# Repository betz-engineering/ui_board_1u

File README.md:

# ui_board_1u
A versatile user interface PCB, specifically designed for integration into the front-panel of a 1U height chassis.

__Featuring__

  * Rotary encoder
  * 2x RGB LEDs, brought to the front with light-pipes for mounting flexibility
  * 1x Tactile push button
  * 2.8" diagonal, 256 x 64 pixel OLED display with 16 shades (SSD1322)
  * All connected to a single 12 pin PMOD port

[__Schematic__](pics/ui_board_1u.pdf)

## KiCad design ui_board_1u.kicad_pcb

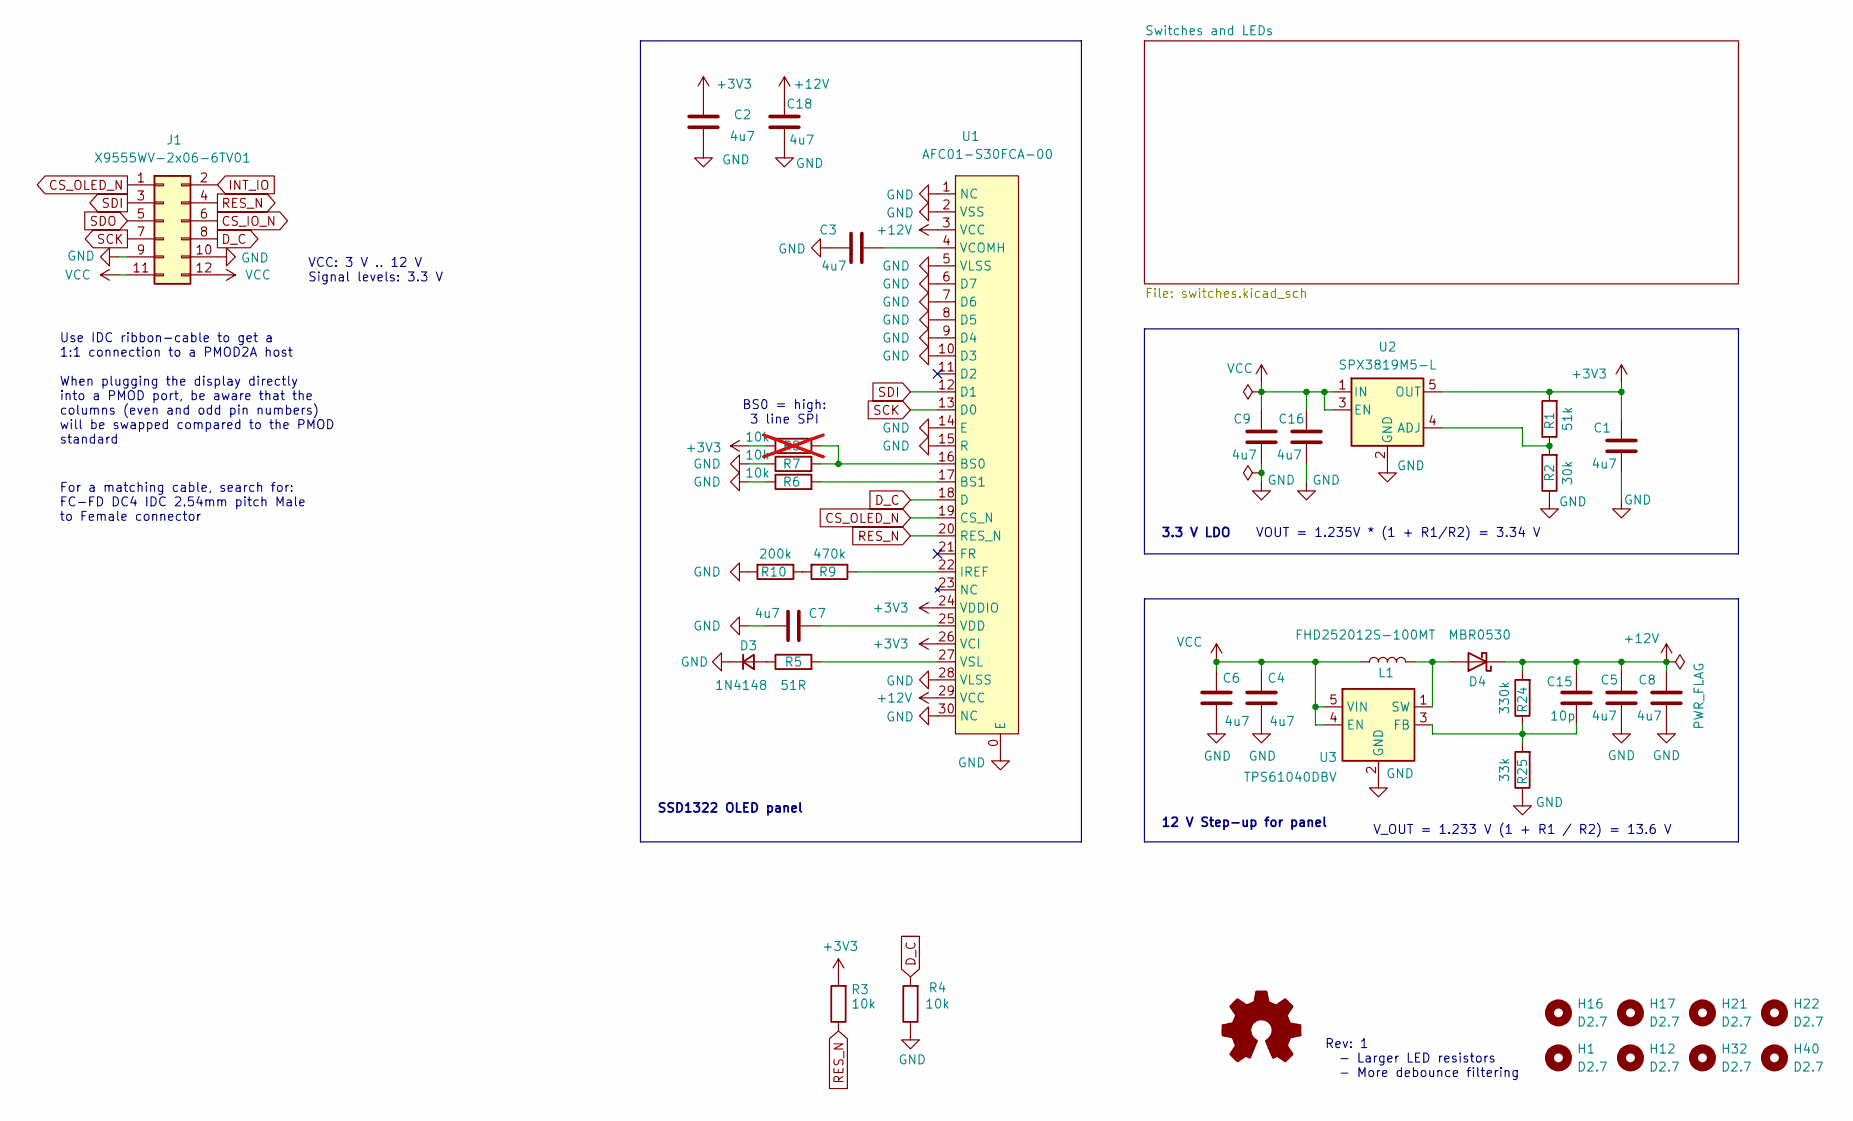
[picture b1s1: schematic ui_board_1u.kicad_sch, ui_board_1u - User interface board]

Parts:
C1, C2, C3, C4, C5, C6, C7, C8, C9, C16, C18: 4u7; C_1206_3216Metric
C15: 10p; C_0603_1608Metric
D3: 1N4148; D_SOD-323F
D4: MBR0530; D_SOD-123
H1, H12, H32, H40: D2.7; MountingHole_2.7mm_M2.5_ISO7380
H16, H17, H21, H22: D2.7; MountingHole_2.7mm_M2.5_ISO7380_Pad
J1: X9555WV-2x06-6TV01; IDC-Header_2x06_P2.54mm_Vertical
L1: FHD252012S-100MT; L_1008_2520Metric
R1: 51k; R_0603_1608Metric
R2: 30k; R_0603_1608Metric
R3, R4, R6, R7: 10k; R_0603_1608Metric
R5: 51R; R_0603_1608Metric
R8: 10k; R_0603_1608Metric; not fitted
R9: 470k; R_0603_1608Metric
R10: 200k; R_0603_1608Metric
R24: 330k; R_0603_1608Metric
R25: 33k; R_0603_1608Metric
U1: AFC01-S30FCA-00; oled_frame_2.8
U2: SPX3819M5-L; SOT-23-5; LCSC Part # C9056
U3: TPS61040DBV; SOT-23-5

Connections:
+3V3: C1.1, C2.1, R1.2, R3.2, R8.1, U1.24 (VDDIO), U1.26 (VCI), U2.5 (OUT); also elsewhere on the board
+12V: C5.1, C8.1, C15.1, C18.1, D4.1 (K), R24.2, U1.3 (VCC), U1.29 (VCC)
CS_IO_N: J1.6; also elsewhere on the board
CS_OLED_N: J1.1, U1.19 (CS_N)
D_C: J1.8, R4.2, U1.18 (D)
GND: C1.2, C2.2, C3.2, C4.2, C5.2, C6.2, C7.2, C8.2, C9.2, C16.2, C18.2, D3.1 (K), J1.9, J1.10, R2.1, R4.1, R6.1, R7.1, R10.2, R25.1, U1.0 (E), U1.1 (NC), U1.2 (VSS), U1.5 (VLSS), U1.6 (D7), U1.7 (D6), U1.8 (D5), U1.9 (D4), U1.10 (D3), U1.14 (E), U1.15 (R), U1.28 (VLSS), U1.30 (NC), U2.2 (GND), U3.2 (GND); also elsewhere on the board
INT_IO: J1.2; also elsewhere on the board
unnamed: D3.2 (A), R5.1
unnamed: D4.2 (A), L1.2, U3.1 (SW)
unnamed: R9.2, R10.1
unnamed: R7.2, R8.2, U1.16 (BS0)
unnamed: R6.2, U1.17 (BS1)
unnamed: R9.1, U1.22 (IREF)
unnamed: C3.1, U1.4 (VCOMH)
unnamed: C7.1, U1.25 (VDD)
unnamed: R5.2, U1.27 (VSL)
unnamed: R1.1, R2.2, U2.4 (ADJ)
unnamed: C15.2, R24.1, R25.2, U3.3 (FB)
RES_N: J1.4, R3.1, U1.20 (RES_N); also elsewhere on the board
SCK: J1.7, U1.13 (D0); also elsewhere on the board
SDI: J1.3, U1.12 (D1); also elsewhere on the board
SDO: J1.5; also elsewhere on the board
VCC: C4.1, C6.1, C9.1, C16.1, J1.11, J1.12, L1.1, U2.1 (IN), U2.3 (EN), U3.4 (EN), U3.5 (VIN)

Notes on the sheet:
12 V Step-up for panel
V_OUT = 1.233 V (1 + R1 / R2) = 13.6 V
Rev: 1 - Larger LED resistors - More debounce filtering
3.3 V LDO
Use IDC ribbon-cable to get a 1:1 connection to a PMOD2A host When plugging the display directly into a PMOD port, be aware that the columns (even and odd pin numbers) will be swapped compared to the PMOD standard
SSD1322 OLED panel
For a matching cable, search for: FC-FD DC4 IDC 2.54mm pitch Male to Female connector
BS0 = high: 3 line SPI
VOUT = 1.235V * (1 + R1/R2) = 3.34 V
VCC: 3 V .. 12 V Signal levels: 3.3 V

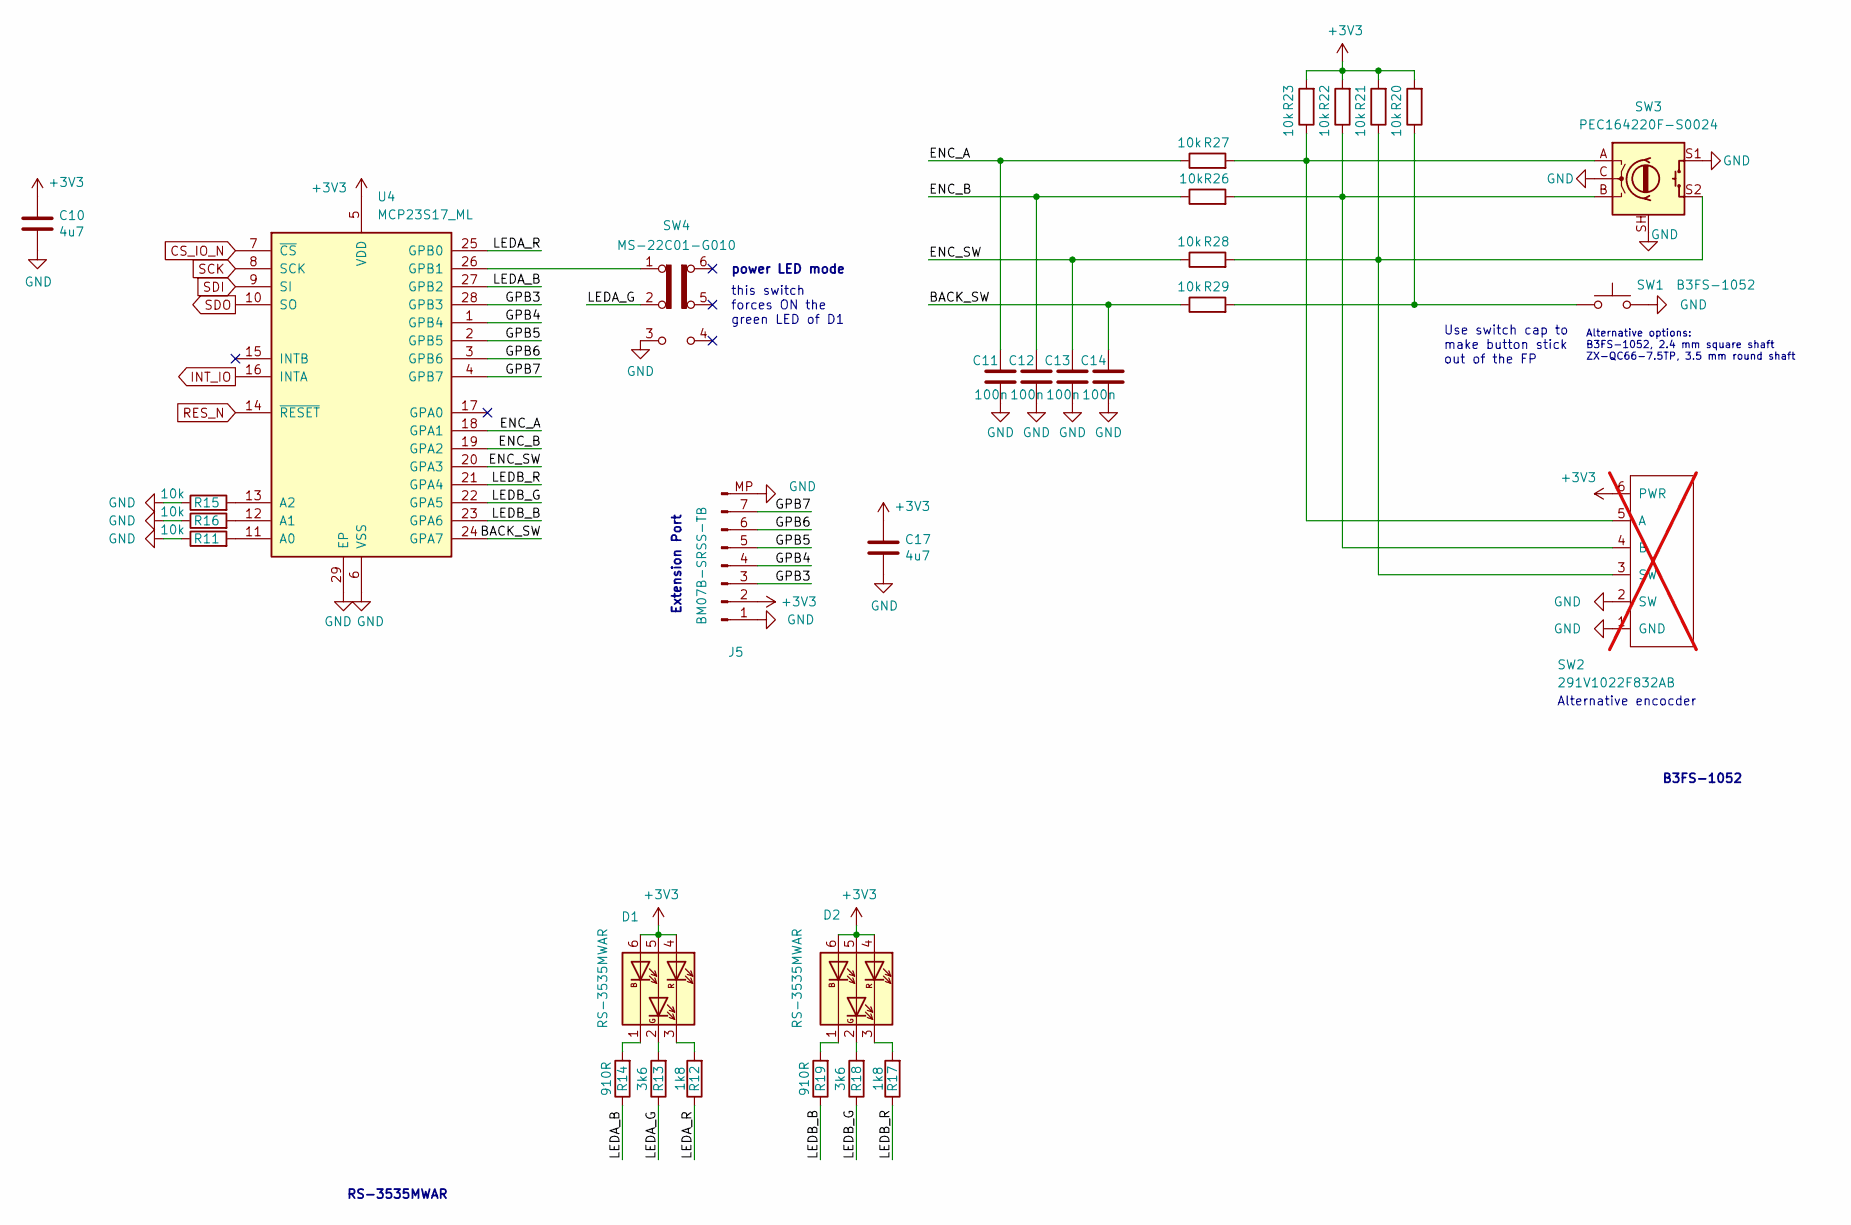
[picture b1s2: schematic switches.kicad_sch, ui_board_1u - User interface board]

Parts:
C10, C17: 4u7; C_1206_3216Metric
C11, C12, C13, C14: 100n; C_0603_1608Metric
D1, D2: RS-3535MWAR; LED_RGB_PLCC-6
J5: BM07B-SRSS-TB; JST_SH_BM07B-SRSS-TB_1x07-1MP_P1.00mm_Vertical; LCSC Part # C160393
R11, R15, R16, R20, R21, R22, R23, R26, R27, R28, R29: 10k; R_0603_1608Metric
R12, R17: 1k8; R_0603_1608Metric
R13, R18: 3k6; R_0603_1608Metric
R14, R19: 910R; R_0603_1608Metric
SW1: B3FS-1052; SW_SPST_Omron_B3FS-105xP
SW2: 291V1022F832AB; 291V1; digikey CT3044-ND; not fitted
SW3: PEC164220F-S0024; RotaryEncoder_Bourns_Vertical_PEC16-4xxxF-Sxxxx
SW4: MS-22C01-G010; MS-22C01
U4: MCP23S17_ML; QFN-28-1EP_6x6mm_P0.65mm_EP4.25x4.25mm

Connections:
+3V3: C10.1, C17.1, D1.4 (AR), D1.5 (AG), D1.6 (AB), D2.4 (AR), D2.5 (AG), D2.6 (AB), J5.2, R20.2, R21.2, R22.2, R23.2, SW2.6 (PWR), U4.5 (VDD); also elsewhere on the board
/Switches and LEDs/BACK_SW: C14.1, R29.1, U4.24 (GPA7)
/Switches and LEDs/ENC_A: C11.1, R27.1, U4.18 (GPA1)
/Switches and LEDs/ENC_B: C12.1, R26.1, U4.19 (GPA2)
/Switches and LEDs/ENC_SW: C13.1, R28.1, U4.20 (GPA3)
/Switches and LEDs/GPB3: J5.3, U4.28 (GPB3)
/Switches and LEDs/GPB4: J5.4, U4.1 (GPB4)
/Switches and LEDs/GPB5: J5.5, U4.2 (GPB5)
/Switches and LEDs/GPB6: J5.6, U4.3 (GPB6)
/Switches and LEDs/GPB7: J5.7, U4.4 (GPB7)
/Switches and LEDs/LEDA_B: R14.1, U4.27 (GPB2)
/Switches and LEDs/LEDA_G: R13.1, SW4.2 (B)
/Switches and LEDs/LEDA_R: R12.1, U4.25 (GPB0)
/Switches and LEDs/LEDB_B: R19.1, U4.23 (GPA6)
/Switches and LEDs/LEDB_G: R18.1, U4.22 (GPA5)
/Switches and LEDs/LEDB_R: R17.1, U4.21 (GPA4)
CS_IO_N: U4.7 (~CS); also elsewhere on the board
GND: C10.2, C11.2, C12.2, C13.2, C14.2, C17.2, J5.1, J5.MP, R11.1, R15.1, R16.1, SW1.2, SW2.1 (GND), SW2.2 (SW), SW3.C, SW3.S1, SW3.SH, SW4.3 (C), U4.6 (VSS), U4.29 (EP); also elsewhere on the board
INT_IO: U4.16 (INTA); also elsewhere on the board
unnamed: D1.1 (KB), R14.2
unnamed: D1.2 (KG), R13.2
unnamed: D1.3 (KR), R12.2
unnamed: D2.1 (KB), R19.2
unnamed: D2.2 (KG), R18.2
unnamed: D2.3 (KR), R17.2
unnamed: R20.1, R29.2, SW1.1
unnamed: R21.1, R28.2, SW2.3 (SW), SW3.S2
unnamed: R23.1, R27.2, SW2.5 (A), SW3.A
unnamed: R22.1, R26.2, SW2.4 (B), SW3.B
unnamed: R11.2, U4.11 (A0)
unnamed: R16.2, U4.12 (A1)
unnamed: R15.2, U4.13 (A2)
unnamed: SW4.1 (A), U4.26 (GPB1)
RES_N: U4.14 (~RESET); also elsewhere on the board
SCK: U4.8 (SCK); also elsewhere on the board
SDI: U4.9 (SI); also elsewhere on the board
SDO: U4.10 (SO); also elsewhere on the board

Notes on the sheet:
B3FS-1052
RS-3535MWAR
Extension Port
this switch forces ON the green LED of D1
Alternative options: B3FS-1052, 2.4 mm square shaft ZX-QC66-7.5TP, 3.5 mm round shaft
Use switch cap to make button stick out of the FP
power LED mode
Alternative encocder

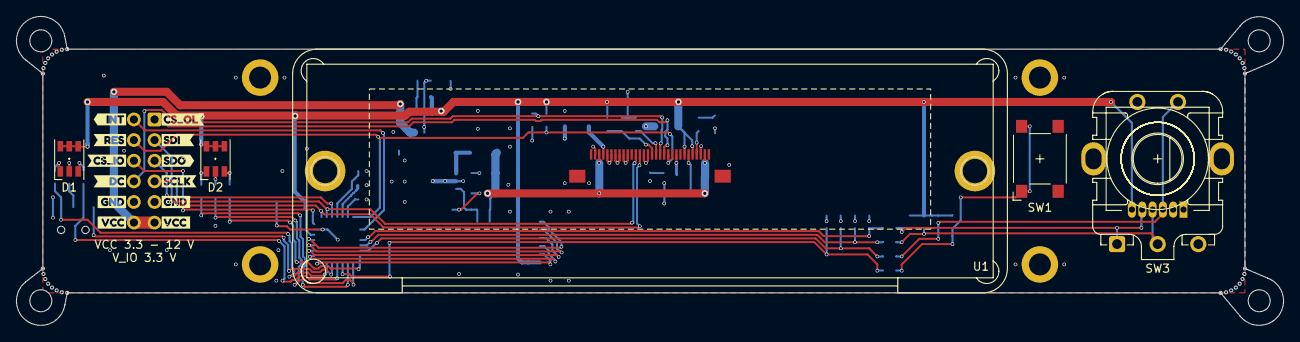
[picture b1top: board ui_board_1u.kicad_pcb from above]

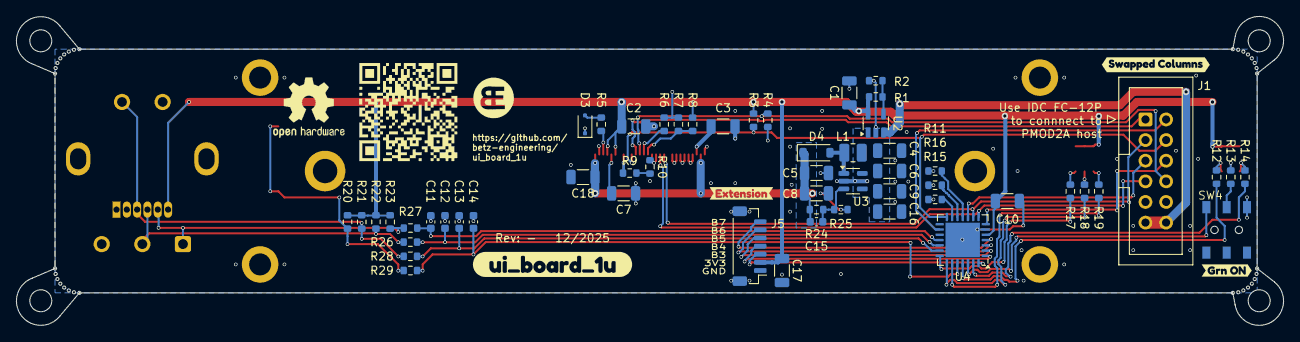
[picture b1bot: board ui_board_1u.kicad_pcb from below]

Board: 2 copper layers, 156.0 x 38.0 mm, 121 parts (63 on the bottom side), 52 nets.

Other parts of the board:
G0, G1: LOGO
G2: OSHW-Logo2_9.8x8mm_SilkScreen
H2, H3, H4, H5, H6, H7, H8, H9, H10, H11, H13, H14, H15, H18, H19, H20, H23, H24, H25, H26, H27, H28, H29, H30, H31, H33, H34, H35, H36, H37, H38, H39: mouse_bite
kibuzzard-1: G***; kibuzzard-693D4C30
kibuzzard-2: G***; kibuzzard-6940589C
kibuzzard-3: G***; kibuzzard-693D4C36
kibuzzard-4: G***; kibuzzard-69405870
kibuzzard-5: G***; kibuzzard-69405890
kibuzzard-6: G***; kibuzzard-6940587B
kibuzzard-7: G***; kibuzzard-693D4C42
kibuzzard-8: G***; kibuzzard-693D4BEE
kibuzzard-9: G***; kibuzzard-693D4C48
kibuzzard-10: G***; kibuzzard-693D4BE6
kibuzzard-11: G***; kibuzzard-693D4C4F
kibuzzard-12: G***; kibuzzard-693D4BDF
kibuzzard-13: G***; kibuzzard-693D4AF8
kibuzzard-14: G***; kibuzzard-693EBA51
kibuzzard-15: G***; kibuzzard-693D4DAF
kibuzzard-69483936: G***; kibuzzard-69483936

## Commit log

2025-12-14 fix 3D models
2025-12-14 add QR code to silkscreen, add render images
2025-12-14 optimize component values for easier production
2025-12-14 add Schematic .pdf
2025-12-14 update Schematic sheet
2025-12-14 oled_panel_frame.scad: remove redundant code
2025-12-15 rename POCI and PICO signals to SDO and SDI
    according to the OSHWA recommendation
    https://oshwa.org/resources/a-resolution-to-redefine-spi-signal-names/
2025-12-15 fix / ignore all remaining DRC errors
2025-12-15 geographical re-annotate
2025-12-15 update schematic .pdf and pictures
2025-12-17 review OLED pinout, add 2 GND pins
2025-12-17 add extension board connector
2025-12-17 fix typo in schematic
2025-12-17 fix some more typos in the schematic
2025-12-21 add button cap for Omron button
2025-12-21 Make button cap longer. Update 3D models
2025-12-21 fine tune ext. con position and silk screen
    rev - ready to order
2025-12-23 add drawing for front-panel cut-outs in User.Comments and Eco1 layers
2025-12-23 button-cap: change outer diameter from 5.0 to 4.6 mm
2025-12-26 cutout drawing: update, snap to grid
    also add exmaple front panel designer file
2025-12-26 update most of the .step files
    * button_cap and oled_frame: update ot the final dimensions
    * oled_panel: add color to the active area
    * add example front-panel .step
2025-12-26 remove unused 2U example panel
2025-12-27 move step file to website
2026-02-03 switch to 4 layers, rough routing done
2026-05-08 oled_panel_frame: add square nut retainer
2026-05-08 rev1, port to kicad 10
    * revise LED resistor values. They were much to bright.
    * Change debouncing filter cap. from 10 nF to 100 nF
    * change to kicad 10
2026-05-08 PCB: sync with schematic. Upgrade to kicad 10
